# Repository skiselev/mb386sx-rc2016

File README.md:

# Alsea River 386SX Motherboard
An 386SX/486SLC Motherboard based on SARC RC2016 Chipset

## Introduction

The origin of this project is the [M396F motherboard replica by Marco Both](https://github.com/Marco-Both/M396F-Replika). Marco replicated the PCB layout of a certain revision of M396F motherboard. He didn't provide the schematic.

I reverse engineered the schematic based on his PCB layout and made a PCB layout using that schematic similar to the Marco's replica. This was the initial version of this project - [version 1.0](https://github.com/skiselev/mb386sx-rc2016/tree/v1.0).

The subsequent versions contain the following improvements:

* Use Dallas DS12885 RTC/NVRAM (aka CMOS) with a CR2032 battery instead of Motorola MC146818 with a NiCad battery. This reduces the likliehood of motherboard damage due to a leaking battery. A more modern RTC IC also reduces the number of components
* Use SST39SF010A Flash ROM instead of an EPROM or OTP ROM. The Flash ROM is in-circuit programmable, allowing BIOS and BIOS extension upgrades. It has a bigger 128 KiB capacity, all of which is mapped to the CPU memory. The SST39SF010A is a currently manufactured part
* Use PS/2 compatible keyboard controller, VIA VT82C42N or similar. The motherboard implements a dual PS/2 port with both keyboard and mouse signals. A PS/2 keyboard/mouse splitter cable can be used to connect both a keyboard and a mouse.
* Use ATX case compatible mounting holes placement. Implement ATX power supply power on circuit. This allows using the motherboard with more modern ATX cases and power supplies
* Use DIP-8 / half-can crystal oscillators for the CPU and FPU clocks. This removes the need for a difficult to get clock synthesizer IC used in the original motherboard, while still allowing changing the CPU and the FPU clock by switching the oscillators
* Implement headers for the CPU. The CPU can be either installed on a [386SX Universal Socket Adapter](https://github.com/skiselev/i386sx-socket), or soldered down on the motherboard
* On board disagnostic LEDs, Power, and Reset switches

## Status

* Board version 2.3 tested and works properly.
* Board version 2.2 has the fix for the BIOS /OE issue, but it has not been actually built and tested yet.
* Board version 2.1 boots up to BIOS, DOS, and Linux, after performing the fix described in the Known Issues section.
* The following CPUs have been tested with the board version 2.1:
  * Intel 386SX, part name: NG80386SX33. Installed on a 386SX Universal Socket Adapter, configured for 5V. Runs well at 33 MHz.
  * Texas Instruments 486SLCX2-50, part name: TI486SXLC2-G50-WN. Installed on a 386SX Universal Socket Adapter, configured for 3.3V. Runs well at 25 MHz, 33 MHz, and 40 MHz. Unable to enable clock doubling yet.
  * Texas Instruments 486SLCX2-50, part name: TI486SXLC2-G50-PQ. Installed on a 386SX Universal Socket Adapter, configured for 3.3V. Runs well at 25 MHz, 33 MHz, and 40 MHz. Unable to enable clock doubling yet.
  * Texas Instruments 486SLC/E-33. part name: TX486SLC/E-33PAF. Installed on a 386SX Universal Socket Adapter, configured for 5V. Runs well at 33 MHz. Also works at 40 MHz, although gets quite hot. Stability has not been verified yet with 40 MHz.
* PS/2 mouse tested and works properly with both 2 button and 3 button wheeled mouse using [CuteMouse driver](https://cutemouse.sourceforge.net/).
* AMI BIOS 5.10 and [Award BIOS 4.50](https://github.com/skiselev/mb386sx-rc2016/tree/main/BIOS) from other SARC RC2016 based motherboards tested. The latter provides better configurability using MODBIN.

## Hardware Documentation

* [Alsea River 386SX Motherboard - User Guide](User_Guide.md)
* [SARC RC2016 Chipset](SARC_RC2016.md)
* [Cyrix and TI 486SLC/SXLC Processors](Cyrix_and_TI_486.md)

### Schematic and PCB Layout

* [Schematic - Version 2.3](KiCad/AT386SX-Schematic-2.3.pdf)
* [PCB Layout - Version 2.3](KiCad/AT386SX-Board-2.3.pdf)

### Bill of Materials

#### Version 2.3

[Alsea River 386SX Motherboard project on Mouser.com](https://www.mouser.com/Tools/Project/Share?AccessID=6eadf3eb2e) - View and order most components except of the CPU, chipset, keyboard controller, SIMM-30 sockets, and the PCB.

Component type     | Reference | Description                                          | Quantity | Possible sources and notes 
------------------ | --------- | ---------------------------------------------------- | -------- | --------------------------
PCB                |           | Alsea River 386SX PCB - Version 2.1                  | 1        | Order from a PCB manufacturer of your choice using provided Gerber or KiCad files
Integrated Circuit | U1        | 386SX CPU, TI486SXLC, Cx486SLC CPU, 100 pin BQFP     | 1        | eBay
Integrated Circuit | U2        | 387SX FPU or compatible, 68 pin PLCC                 | 1        | eBay. Optional
Integrated Circuit | U3        | SARC RC2016A5, 208 pin PQFP                          | 1        | UTsource
Integrated Circuit | U4        | DS12885 RTC, 24 pin DIP                              | 1        | Mouser [700-DS12885](https://www.mouser.com/ProductDetail/700-DS12885)
Integrated Circuit | U5        | VT82C42N keyboard/mouse controller, 40 pin DIP       | 1        | eBay
Integrated Circuit | U6        | SST39SF010A 128 KiB Flash ROM, 32 pin DIP            | 1        | Mouser [804-39SF010A7CPHE](https://www.mouser.com/ProductDetail/804-39SF010A7CPHE)
Integrated Circuit | U7        | 74HC05 inverters with open drain outputs, 14 pin DIP | 1        | Mouser [595-SN74AHC05N](https://www.mouser.com/ProductDetail/595-SN74AHC05N), [595-SN74HC05N](https://www.mouser.com/ProductDetail/595-SN74HC05N), [595-SN74LS06N](https://www.mouser.com/ProductDetail/595-SN74LS06N)
Integrated Circuit | U8        | 74HCT14 inverters with Schmitt trigger inputs, 14 pin DIP | 1   | Mouser [595-SN74AHCT14N](https://www.mouser.com/ProductDetail/595-SN74AHCT14N), [595-SN74HCT14N](https://www.mouser.com/ProductDetail/595-SN74HCT14N)
Integrated Circuit | U9        | 74HCT74 D-flip flops, 14 pin DIP                     | 1        | Mouser [595-SN74AHCT74N](https://www.mouser.com/ProductDetail/595-SN74AHCT74N), [595-SN74HCT74N](https://www.mouser.com/ProductDetail/595-SN74HCT74N), 
Integrated Circuit | U10       | LM7905 -5V voltage regulator, TO-220-3               | 1        | Mouser [863-MC7905CTG](https://www.mouser.com/ProductDetail/863-MC7905CTG), [926-LM7905CT/NOPB](https://www.mouser.com/ProductDetail/926-LM7905CT-NOPB)
Transistor         | Q1        | 2N3904, NPN transistor, TO-92                        | 1        | Mouser [512-2N3904TA](https://www.mouser.com/ProductDetail/512-2N3904TA)
LED                | D1        | 3 mm LED, blue                                       | 1        | Optional. Mouser [604-WP710A10QBD/D](https://www.mouser.com/ProductDetail/604-WP710A10QBD-D), [696-SSL-LX3054USBD](https://www.mouser.com/ProductDetail/696-SSL-LX3054USBD), [749-3BWD-S](https://www.mouser.com/ProductDetail/749-3BWD-S)
LED                | D2        | 3 mm LED, bi-color red/green                         | 1        | Optional. Mouser [604-WP937EGW](https://www.mouser.com/ProductDetail/604-WP937EGW), [696-SSL-LX3054IGW](https://www.mouser.com/ProductDetail/696-SSL-LX3054IGW), [749-3BC](https://www.mouser.com/ProductDetail/749-3BC)
LED Spacer         | D1, D2    | Spacer for 3 mm LEDs, 3mm height                     | 2        | Optional. Mouser [749-ELM-2-3MM](https://www.mouser.com/ProductDetail/749-ELM-2-3MM)
Crystal Oscillator | X1        | 66 MHz (twice desired CPU frequency), 5V, DIP-8      | 1        | Mouser 50 MHz: [520-TCH5000](https://www.mouser.com/ProductDetail/520-TCH5000), [815-ACH-50-EK](https://www.mouser.com/ProductDetail/815-ACH-50-EK), [774-MXO45HS-3C-50.0](https://www.mouser.com/ProductDetail/774-MXO45HS-3C-50.0); 66.6666MHz: [774-MXO45HS2C66.6666](https://www.mouser.com/ProductDetail/774-MXO45HS2C66.6666), [520-TCH6666-X](https://www.mouser.com/ProductDetail/520-TCH6666-X); 80 MHz: [520-ECS-2200B-800](https://www.mouser.com/ProductDetail/520-ECS-2200B-800), [774-MXO45HS-3C-80.0](https://www.mouser.com/ProductDetail/774-MXO45HS-3C-80.0)
Crystal Oscillator | X2        | 66 MHz (twice desired FPU frequency), 5V, DIP-8      | 1        | Optional. See above.
Crystal Resonator  | Y1        | 14.31818 MHz, parallel, HC-49U                       | 1        | Mouser [815-ABL-14.31818B2](https://www.mouser.com/ProductDetail/815-ABL-14.31818B2), [559-FOXS143-20-LF](https://www.mouser.com/ProductDetail/559-FOXS143-20-LF)
Crystal Resonator Insulator | Y1 | Mylar insulator for HC-49U crystal resonators      | 1        | Optional. Mouser [749-CI-192-028-SR](https://www.mouser.com/ProductDetail/749-CI-192-028-SR)
Crystal Resonator  | Y2        | 32768 Hz, watch crystal, 6 pf, D = 2.1 mm, L = 6.2 mm  | 1      | Mouser [815-AB26T32768KHZ6B](https://www.mouser.com/ProductDetail/815-AB26T32768KHZ6B), [520-ECS327-6-13-X](https://www.mouser.com/ProductDetail/520-ECS327-6-13-X), or [628-VT200F-6PF20PPM](https://www.mouser.com/ProductDetail/628-VT200F-6PF20PPM)
IC Socket          | U2        | 68 pin PLCC, through hole                            | 1        | Mouser [737-PLCC-68-AT](https://www.mouser.com/ProductDetail/737-PLCC-68-AT), [517-8468-11B1-RK-TP](https://www.mouser.com/ProductDetail/517-8468-11B1-RK-TP), [575-682444](https://www.mouser.com/ProductDetail/575-682444)
IC Socket          | U4        | 24 pin DIP                                           | 1        | Mouser [737-ICS-624-T](https://www.mouser.com/ProductDetail/737-ICS-624-T), [517-4824-6000-CP](https://www.mouser.com/ProductDetail/517-4824-6000-CP), [571-1-2199298-8](https://www.mouser.com/ProductDetail/571-1-2199298-8)
IC Socket          | U5        | 40 pin DIP                                           | 1        | Mouser [737-ICS-640-T](https://www.mouser.com/ProductDetail/737-ICS-640-T), [517-4840-6000-CP](https://www.mouser.com/ProductDetail/517-4840-6000-CP), [571-1-2199299-5](https://www.mouser.com/ProductDetail/571-1-2199299-5)
IC Socket          | U6        | 32 pin DIP                                           | 1        | Mouser [737-ICS-632-T](https://www.mouser.com/ProductDetail/737-ICS-632-T), [517-4832-6000-CP](https://www.mouser.com/ProductDetail/517-4832-6000-CP), [571-1-2199300-2](https://www.mouser.com/ProductDetail/571-1-2199300-2)
IC Socket          | U7 - U9   | 14 pin DIP                                           | 3        | Mouser [737-ICS-314-T](https://www.mouser.com/ProductDetail/737-ICS-314-T), [517-4814-3000-CP](https://www.mouser.com/ProductDetail/517-4814-3000-CP), [571-1-2199298-3](https://www.mouser.com/ProductDetail/571-1-2199298-3)
Oscillator Socket  | X1, X2    | 4 pin DIP                                            | 2        | Mouser [535-1108800](https://www.mouser.com/ProductDetail/535-1108800)
Battery            | BT1       | CR2032 battery                                       | 1        | Mouser [81-CR2032](https://www.mouser.com/ProductDetail/81-CR2032), [658-CR2032](https://www.mouser.com/ProductDetail/658-CR2032), [614-CR2032-200](https://www.mouser.com/ProductDetail/614-CR2032-200)
Battery Socket     | BT1       | CR2032 battery socket, through hole                  | 1        | Mouser [122-2420-GR](https://www.mouser.com/ProductDetail/122-2420-GR), [122-2620-GR](https://www.mouser.com/ProductDetail/122-2620-GR)
Connector          | J1 - J4   | SIMM 30 socket, 30 pin                               | 4        | eBay
Connector          | J5 - J10  | ISA card edge connector, 98 pin                      | 6        | Mouser [587-395-098-520-350](https://www.mouser.com/ProductDetail/587-395-098-520-350)
Connector          | J11       | PS/2 Keyboard/Mouse connector, Mini-DIN 6 pin        | 1        | Mouser [806-KMDGX-6S-BS](https://www.mouser.com/ProductDetail/806-KMDGX-6S-BS)
Connector          | J12       | ATX power connector, 20 pin                          | 1        | Mouser [538-46015-2006](https://www.mouser.com/ProductDetail/538-46015-2006)
Connector          | J13       | 2x8 pin header, 2.54 mm (0.1") pitch, through hole   | 1        | Mouser [737-PH2-16-UA](https://www.mouser.com/ProductDetail/737-PH2-16-UA)
Connector          | J14 - J17 | 2x14 pin socket, 2 mm pitch, through hole            | 4        | Optional. Mouser [538-79107-7062](https://www.mouser.com/ProductDetail/538-79107-7062), [200-SQT11301LD](https://www.mouser.com/ProductDetail/200-SQT11301LD), [200-SQT11301FD](https://www.mouser.com/ProductDetail/200-SQT11301FD)
Connector          | JP1 - JP3 | 2 pin header, 2.54 mm (0.1") pitch, through hole     | 3        | Mouser [737-PH1-02-UA](https://www.mouser.com/ProductDetail/737-PH1-02-UA)
Connector          | JP4 - JP6 | 3 pin header, 2.54 mm (0.1") pitch, through hole     | 3        | Mouser [737-PH1-03-UA](https://www.mouser.com/ProductDetail/737-PH1-03-UA). Some headers are optional, and can be hardwired for the soldered CPU.
Connector          | JP1 - JP6 | Shunt, 2 pin, 2.54 mm (0.1") pitch                   | 4        | Mouser [737-MSA-G](https://www.mouser.com/ProductDetail/737-MSA-G), [806-SX1100-B](https://www.mouser.com/ProductDetail/806-SX1100-B)
Switch             | SW1, SW2  | 6 mm tactile switch, vertical, through hole          | 2        | Optional. Mouser [653-B3F-1000](https://www.mouser.com/ProductDetail/653-B3F-1000)
Capacitor          | C1 - C3   | 30 pF, 50V MLCC, 5.08 mm (0.2") pitch                | 3        | Mouser [594-K300J10C0GF5UH5](https://www.mouser.com/ProductDetail/594-K300J10C0GF5UH5)
Capacitor          | C4 - C7   | 47 pF, 50V MLCC, 5.08 mm (0.2") pitch                | 4        | Mouser [810-FG28C0G1H470JNT6](https://www.mouser.com/ProductDetail/810-FG28C0G1H470JNT6)
Capacitor          | C8        | 100 pF, 50V MLCC, 5.08 mm (0.2") pitch               | 1        | Mouser [810-FG28C0G1H101JNT6](https://www.mouser.com/ProductDetail/810-FG28C0G1H101JNT6)
Capacitor          | C9        | 220 pF, 50V MLCC, 5.08 mm (0.2") pitch               | 1        | Mouser [810-FG28C0G1H221JNT6](https://www.mouser.com/ProductDetail/810-FG28C0G1H221JNT6)
Capacitor          | C10 - C21 | 100 nF, 25V MLCC, 5.08 mm (0.2") pitch               | 12       | Mouser [594-K104K15X7RF53H5](https://www.mouser.com/ProductDetail/594-K104K15X7RF53H5), [810-FG28X7R1H104KNT6](https://www.mouser.com/ProductDetail/810-FG28X7R1H104KNT6)
Capacitor          | C22, C23  | 1 uF, 10V MLCC, 5.08 mm (0.2") pitch                 | 2        | Mouser [810-FG28X5R1H105KRT6](https://www.mouser.com/ProductDetail/810-FG28X5R1H105KRT6)
Capacitor          | C24 - C48 | 10 uF, 25V electrolytic, 5 mm diameter, 2.5 mm pitch | 25       | Mouser [667-EEU-FR1H100](https://www.mouser.com/ProductDetail/667-EEU-FR1H100)
Polyfuse           | F1        | 1.1A, 5.08 mm (0.2") pitch                           | 1        | Mouser [650-RUSBF110-2](https://www.mouser.com/ProductDetail/650-RUSBF110-2)
Ferrite Choke      | L1 - L4   | axial                                                | 4        | Mouser [623-2743001112LF](https://www.mouser.com/ProductDetail/623-2743001112LF)
Resistor           | R1 - R12  | 10 ohm, 0.25 W, axial                                | 12       | Mouser [708-CF14JT10R0](https://www.mouser.com/ProductDetail/708-CF14JT10R0), [603-MFR-25FBF52-10R](https://www.mouser.com/ProductDetail/603-MFR-25FBF52-10R)
Resistor           | R13 - R15 | 22 ohm, 0.25 W, axial                                | 3        | Mouser [708-CF14JT22R0](https://www.mouser.com/ProductDetail/708-CF14JT22R0), [603-MFR-25FBF52-22R](https://www.mouser.com/ProductDetail/603-MFR-25FBF52-22R)
Resistor           | R16, R17  | 56 ohm, 0.25 W, axial                                | 2        | Mouser [708-CF14JT56R0](https://www.mouser.com/ProductDetail/708-CF14JT56R0), [603-MFR-25FBF52-56R](https://www.mouser.com/ProductDetail/603-MFR-25FBF52-56R)
Resistor           | R18 - R21 | 100 ohm, 0.25 W, axial                               | 4        | Mouser [708-CF14JT100R](https://www.mouser.com/ProductDetail/708-CF14JT100R), [603-MFR-25FBF52-100R](https://www.mouser.com/ProductDetail/603-MFR-25FBF52-100R)
Resistor           | R22       | 330 ohm, 0.25 W, axial                               | 1        | Mouser [708-CF14JT330R](https://www.mouser.com/ProductDetail/708-CF14JT330R), [603-MFR-25FBF52-330R](https://www.mouser.com/ProductDetail/603-MFR-25FBF52-330R)
Resistor           | R23 - R29 | 470 ohm, 0.25 W, axial                               | 7        | Mouser [708-CF14JT470R](https://www.mouser.com/ProductDetail/708-CF14JT470R), [603-MFR-25FBF52-470R](https://www.mouser.com/ProductDetail/603-MFR-25FBF52-470R)
Resistor           | R30, R31  | 1 kohm, 0.25 W, axial                                | 2        | Mouser [708-CF14JT1K00](https://www.mouser.com/ProductDetail/708-CF14JT1K00), [603-MFR-25FBF52-1K](https://www.mouser.com/ProductDetail/603-MFR-25FBF52-1K)
Resistor           | R32       | 4.7 kohm, 0.25 W, axial                              | 1        | Mouser [708-CF14JT4K70](https://www.mouser.com/ProductDetail/708-CF14JT4K70), [603-MFR-25FBF52-4K7](https://www.mouser.com/ProductDetail/603-MFR-25FBF52-4K7)
Resistor           | R33 - R38 | 10 kohm, 0.25 W, axial                               | 6        | Mouser [708-CF14JT10K0](https://www.mouser.com/ProductDetail/708-CF14JT10K0), [603-MFR-25FBF52-10K](https://www.mouser.com/ProductDetail/603-MFR-25FBF52-10K)
Resistor           | R39       | 22 kohm, 0.25 W, axial                               | 1        | Mouser [708-CF14JT22K0](https://www.mouser.com/ProductDetail/708-CF14JT22K0), [603-MFR-25FBF52-22K](https://www.mouser.com/ProductDetail/603-MFR-25FBF52-22K)
Resistor           | R40       | 1 Mohm, 0.25 W, axial                                | 1        | Mouser [708-CF14JT1M00](https://www.mouser.com/ProductDetail/708-CF14JT1M00), [603-MFR-25FBF52-1M](https://www.mouser.com/ProductDetail/603-MFR-25FBF52-1M)
Resistor Array     | RN1       | 330 ohm, 8 resistors, bussed, 9 pin SIL              | 1        | Mouser [652-4609X-1LF-330](https://www.mouser.com/ProductDetail/652-4609X-1LF-330), [652-4609X-AP1-331LF](https://www.mouser.com/ProductDetail/652-4609X-AP1-331LF)
Resistor Array     | RN2, RN3  | 4.7 kohm, 5 resistors, bussed, 6 pin SIL             | 2        | Mouser [652-4606X-1LF-4.7K](https://www.mouser.com/ProductDetail/652-4606X-1LF-4.7K), [652-4606X-AP1-472LF](https://www.mouser.com/ProductDetail/652-4606X-AP1-472LF)
Resistor Array     | RN4       | 4.7 kohm, 8 resistors, bussed, 9 pin SIL             | 1        | Mouser [652-4609X-1LF-4.7K](https://www.mouser.com/ProductDetail/652-4609X-1LF-4.7K), [652-4609X-AP1-472LF](https://www.mouser.com/ProductDetail/652-4609X-AP1-472LF)
Resistor Array     | RN5       | 10 kohm, 4 resistors, bussed, 5 pin SIL              | 1        | Mouser [652-4605X-1LF-10K](https://www.mouser.com/ProductDetail/652-4605X-1LF-10K), [652-4605X-AP1-103LF](https://www.mouser.com/ProductDetail/652-4605X-AP1-103LF)

## Software

### BIOS

For the testing purposes I am using BIOSes from other commerical motherboards based on the same SARC RC2016 chipset. [The Retro Web](https://theretroweb.com/bios?itemsPerPage=24&chipsetIds[]=648) has a collection of the BIOSes for this chipset.

#### BIOS Progamming and ROM ICs support.

The is designed for the 128 KiB SST SST39SF010A Flash ROM. This ROM is mapped to the 0xE0000-0xFFFFF (or, with 8086 segments, E000:0000 to F000:FFFF). The upper 64 KiB - 0xF0000-0xFFFFF (F000:0000-F000:FFFF) are typically used for the BIOS ROM. The lower 64 KiB - 0xE0000-0xEFFFF can be used for BIOS extensions. Please take that into the consideration when programming the Flash ROM. Make sure to load the BIOS image to the top 64 KiB of the Flash ROM, starting at the address 0x10000. Other pin compatible 128 KiB Flash ROMs, such as AMD AM29F010A, SST SST29EE010, Atmel AT29C010A can be also used without any changes.

It is also possible to use 256 KiB and 512 KiB Flash ROMs, for example SST39SF020 and SST39SF040. Note that the A17 address line is connected to VCC (logic high/"1") and the address line A18 is connected to the ground (logic low/"0"). Therefore when using these flash ROMs, please program the 64 KiB BIOS image starting at the addres 0x30000 of the Flash ROM.

Finally, the board also should work with 64 KiB EPROMs and OTP ROMs, e.g., 27C512. In this case, install the EPROM to the right side of the socket, that is pin 1 of the EPROM should go to the pin 3 of the socket.

## Changes

* Version 2.3
  * Use non-plated through holes for the plastic posts of SIMM30 sockets
  * Ground the shield of the PS/2 connector
  * Update silkscreen: Add acknowledgements, move references and values of DRAM resistors to make them more visible
  * Update schematic: Update a few pins on the RC2016A symbol

* Version 2.2
  * Fix the Flash ROM /OE issue: Connect Flash ROM /OE to ISA /MEMR
  * Renumber DRAM banks - swap Bank 0 and Bank 1. Rename DRAM signals accordingly
  * Add CPU pin 1 marking on the silkscreen
  * Renumber SIMM and ISA slots, so that the reference numbers increase from the top of the PCB to the bottom
  * Renumber electrolytic capacitors, so that the reference numbers increase from the top of the PCB to the bottom
  * Use 22 kohm resistor for R39
  * Remove load capacitors on the ISA bus signals, that are not populated anyway
  * Add a polyfuse for the PS/2 port

* Version 2.1
  * Renumber the component references according to the values and locations on the PCB
  * Update silkscreen
  * Add signal names on the back silkscreen

* Version 2.0
  * Use ATX power supply connector
  * Add ATX power-on circuit

* Version 1.9
  * Add pin headers for the CPU

* Version 1.8
  * Connect /OE and /WE of the BIOS ROM to allow Flash ROM in-system programming
  * Rotate the PCB into portrait orientation

* Version 1.7
  * Use single front panel connector

* Version 1.6
  * Use a low profile 14.31818 MHz crystal (or an SMD part)
  * Add support for the separate FPU clock
  * Use half can oscillators for the CPU and the FPU clocks
  * Use discrete resistors for DRAM interface
  * Use resistors with 300 mil (7.62 mm) lead spacing
  * Move R23 down closer to JP8

* Version 1.5
  * Add more 10 uF filtering capacitors to the power rails
  * Remove extra capacitors for /IOW and RESET signals (use capacitors between two leftmost ISA slots
  * Use resistor arrays for SA17-SA19 pull-ups

* Version 1.4
  * Increase board depth by 0.1". Move mount holes to ATX compatible locations

* Version 1.3
  * Wire keyboard controller in PS/2 mode. Use PS/2 Mini-Din connector in a PS/2 dualport configuration

* Version 1.2
  * Add support for 128 KiB Flash ROM ICs for BIOS. SST39SF010A or similar.
 
* Version 1.1
  * Use DS12885 RTC with CR2032 coin cell battery

* Version 1.0
  * Reverse engineered schematic of M396F motherboard
  * PCB layout closely based on the original M396F layout with a few minor changes

## Known Issues

* Versions 1.8 - 2.1
  * The board will not boot into the BIOS.
    * Workaround: Cut the trace going to the Flash ROM pin 24. Solder a wire to connect the flash ROM /OE signal, pin 24 to the ISA /MEMR signal, ISA bus pin 89.
    * The issue happens because following the reset, 386SX fetches instructions starting from address 0xFFFFF0 - the last 16 bytes of its 16 MiB address space. But the board uses /SMEMR signal for the Flash ROM /OE, and that signal is only generated when reading the first megabyte of memory. So the BIOS ROM does not get the /OE signal.

* Versions 1.0 - 2.1
  * DRAM bank 0 and bank 1 swapped around. Bank 0 is the one closer to the edge of the board.

## Wishlist

* On-board speaker
* Try using more common values for C1 - C2: 27 pF or 33 pF are more commonly available than 30 pF
* 3.3V CPU support
  * The current plan is to test this using the [386SX Universal Socket Adapter](https://github.com/skiselev/i386sx-socket)
  * Separate VCC plane for the CPU
  * Linear voltage regulator
  * Solder jumpers to bypass the voltage regulator and connect the CPU to 5V
* 4 layer PCB
  * VCC and ground planes
* Consider using SMD components

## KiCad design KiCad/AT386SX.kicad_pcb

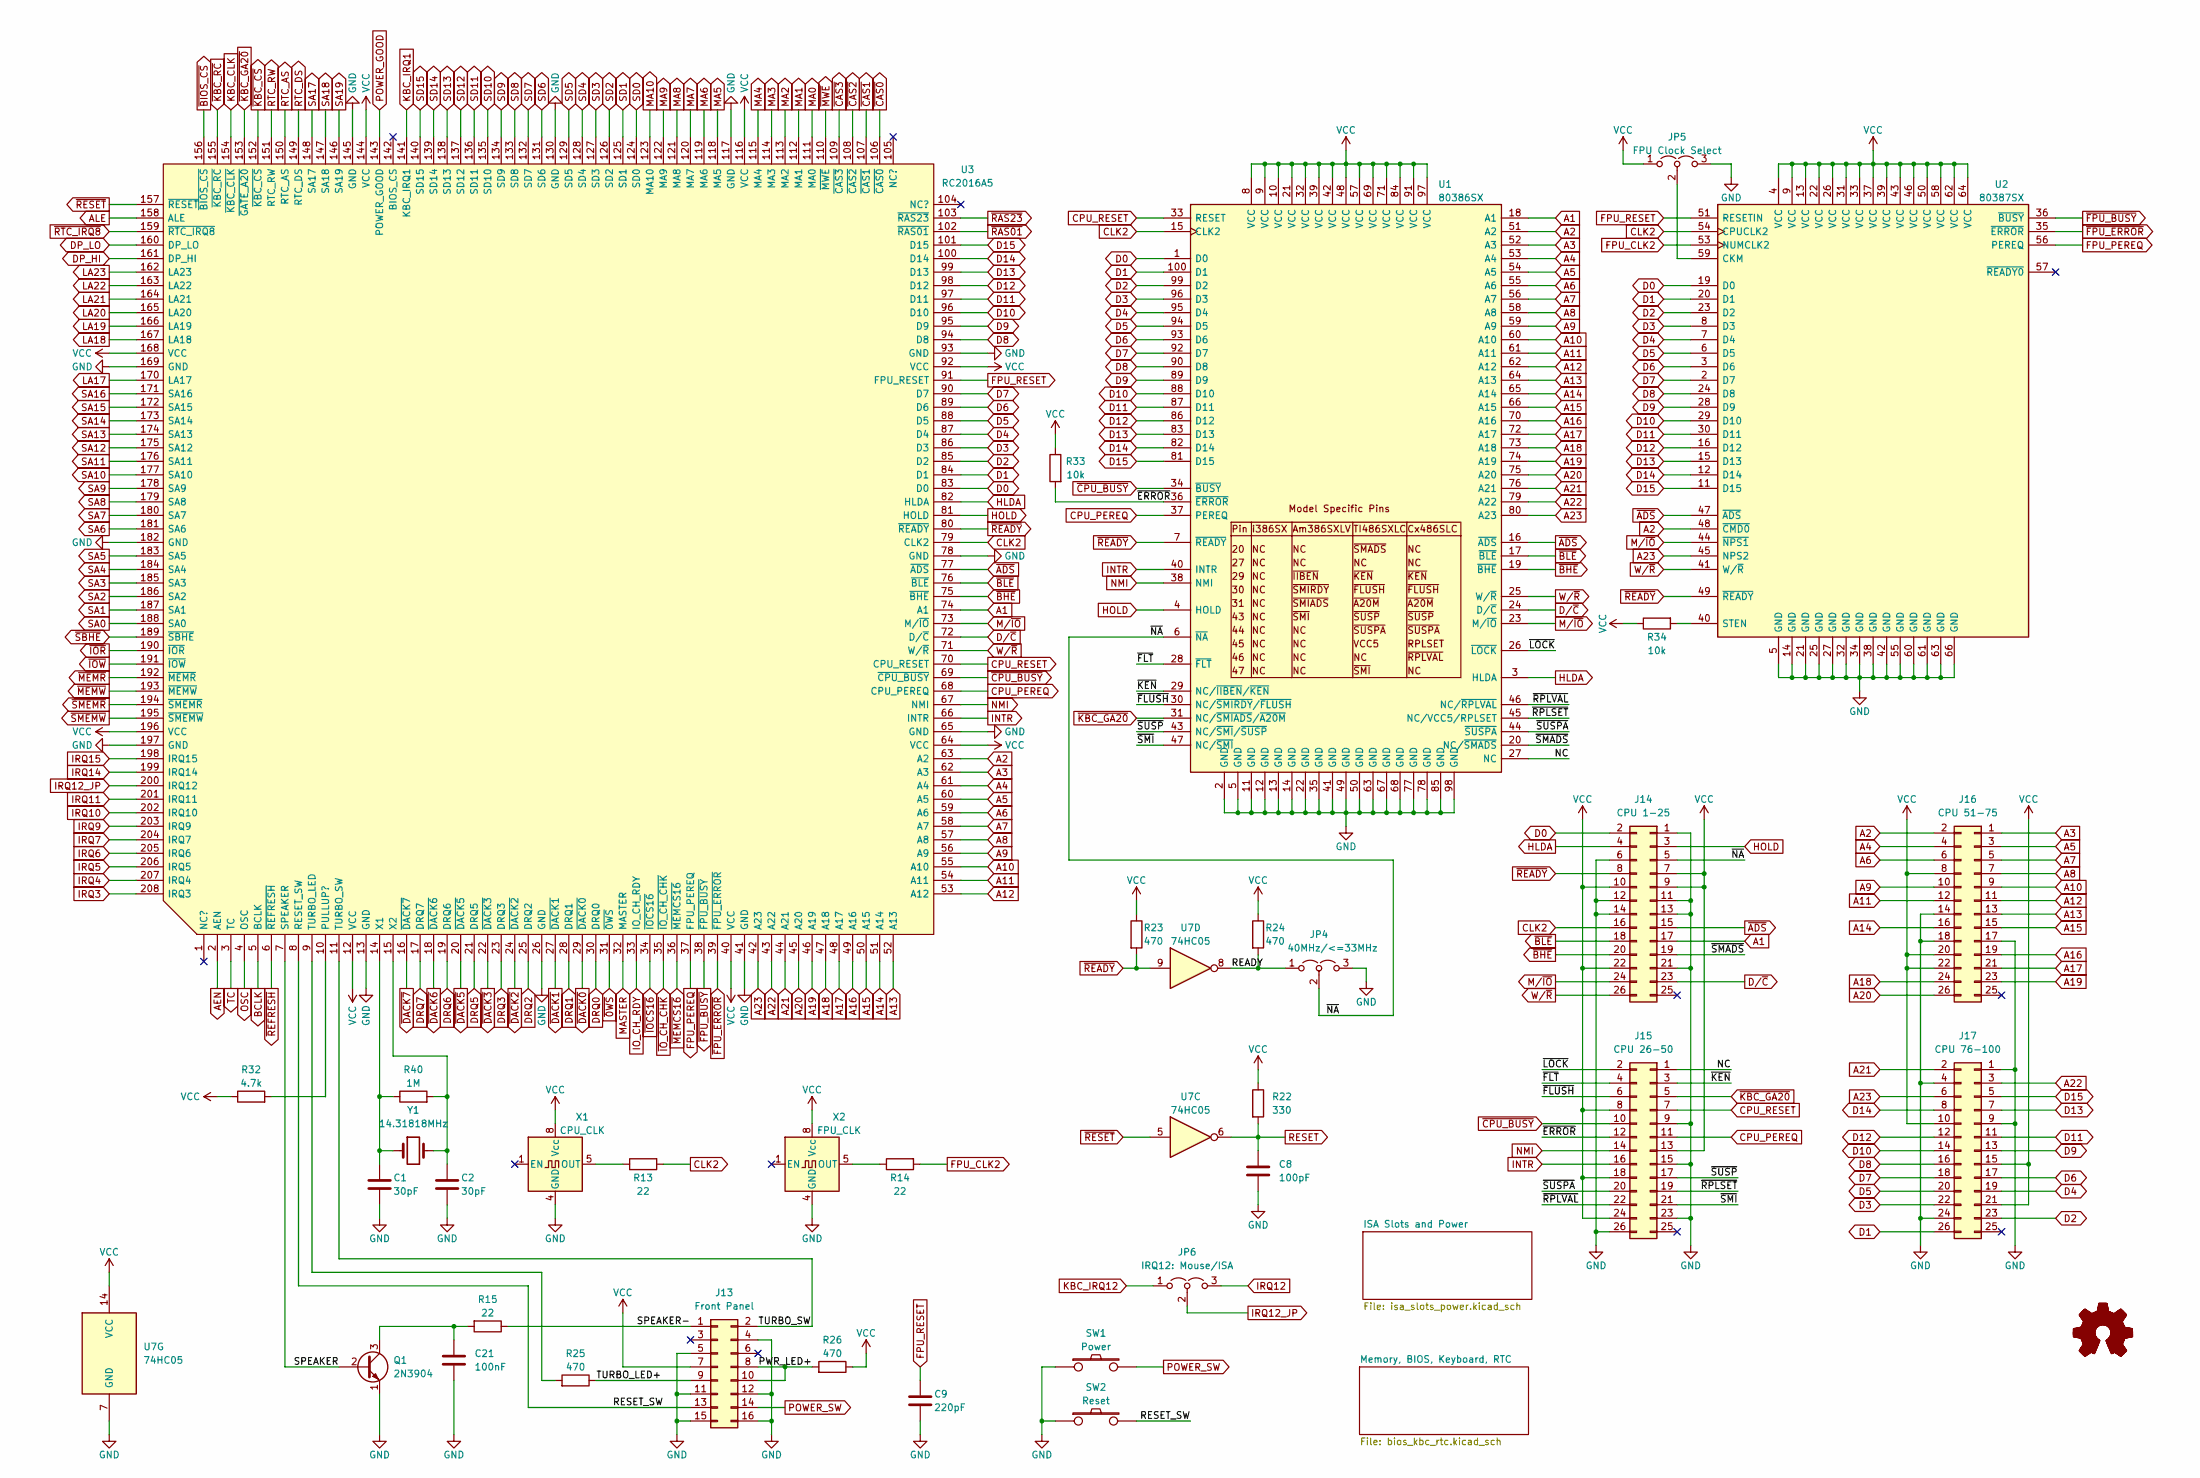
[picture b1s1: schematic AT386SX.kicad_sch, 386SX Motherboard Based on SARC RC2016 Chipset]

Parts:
C1, C2: 30pF; Cap_Cer_508
C8: 100pF; Cap_Cer_508
C9: 220pF; Cap_Cer_508
C21: 100nF; Cap_Cer_508
J13: Front Panel; Conn_Pin_Header_8x2_2.54mm
J14: CPU 1-25; PinHeader_2x13_P2.00mm_Vertical
J15: CPU 26-50; PinHeader_2x13_P2.00mm_Vertical
J16: CPU 51-75; PinHeader_2x13_P2.00mm_Vertical
J17: CPU 76-100; PinHeader_2x13_P2.00mm_Vertical
JP4: 40MHz/<=33MHz; Conn_Pin_Header_3x1_2.54mm
JP5: FPU Clock Select; Conn_Pin_Header_3x1_2.54mm
JP6: IRQ12: Mouse/ISA; Conn_Pin_Header_3x1_2.54mm
LOGO1: Logo_Open_Hardware_Small; OSHW-Logo2_7.3x6mm_SilkScreen
LOGO2: Logo_Open_Hardware_Small; KiCad-Logo2_5mm_SilkScreen
Q1: 2N3904; Transistor_TO92_EBC_254
R13, R14, R15: 22; Res_762
R22: 330; Res_762
R23, R24, R25, R26: 470; Res_762
R32: 4.7k; Res_762
R33, R34: 10k; Res_762
R40: 1M; Res_762
SW1: Power; Switch_Tactile_6mm
SW2: Reset; Switch_Tactile_6mm
U1: 80386SX; PQFP-100_19x19mm_P0.635mm_i386sx
U2: 80387SX; IC_PLCC68_INTEL_TH
U3: RC2016A5; PQFP-208_28x28mm_P0.5mm
U7: 74HC05; IC_DIP14_300
X1: CPU_CLK; OSC_Half_Can_DIP8
X2: FPU_CLK; OSC_Half_Can_DIP8
Y1: 14.31818MHz; Crystal_HC-49U_Vert

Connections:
/NC: J15.1, U1.27 (NC)
/PWR_LED+: J13.8, J13.10, R26.2
/READY: JP4.1 (A), R24.2, U7.8
/RESET_SW: J13.13, SW2.2, U3.8 (RESET_SW)
/SPEAKER: Q1.2 (B), U3.7 (SPEAKER)
/SPEAKER-: J13.1, R15.1
/TURBO_LED+: J13.9, R25.1
/TURBO_SW: J13.2, U3.11 (TURBO_SW)
/~ERROR: J15.12, R33.2, U1.36 (~ERROR)
/~FLT: J15.4, U1.28 (~FLT)
/~FLUSH: J15.6, U1.30 (NC/~SMIRDY/~FLUSH)
/~KEN: J15.3, U1.29 (NC/~IIBEN/~KEN)
/~LOCK: J15.2, U1.26 (~LOCK)
/~NA: J14.5, JP4.2 (C), U1.6 (~NA)
/~RPLSET: J15.19, U1.45 (NC/VCC5/RPLSET)
/~RPLVAL: J15.22, U1.46 (NC/~RPLVAL)
/~SMADS: J14.19, U1.20 (NC/~SMADS)
/~SMI: J15.21, U1.47 (NC/~SMI)
/~SUSPA: J15.20, U1.44 (~SUSPA)
/~SUSP: J15.17, U1.43 (NC/~SMI/~SUSP)
A1: J14.17, U1.18 (A1), U3.74 (A1)
A2: J16.2, U1.51 (A2), U2.48 (~CMD0), U3.63 (A2)
A3: J16.1, U1.52 (A3), U3.62 (A3)
A4: J16.4, U1.53 (A4), U3.61 (A4)
A5: J16.3, U1.54 (A5), U3.60 (A5)
A6: J16.6, U1.55 (A6), U3.59 (A6)
A7: J16.5, U1.56 (A7), U3.58 (A7)
A8: J16.7, U1.58 (A8), U3.57 (A8)
A9: J16.10, U1.59 (A9), U3.56 (A9)
A10: J16.9, U1.60 (A10), U3.55 (A10)
A11: J16.12, U1.61 (A11), U3.54 (A11)
A12: J16.11, U1.62 (A12), U3.53 (A12)
A13: J16.13, U1.64 (A13), U3.52 (A13)
A14: J16.16, U1.65 (A14), U3.51 (A14)
A15: J16.15, U1.66 (A15), U3.50 (A15)
A16: J16.19, U1.70 (A16), U3.49 (A16)
A17: J16.21, U1.72 (A17), U3.48 (A17)
A18: J16.24, U1.73 (A18), U3.47 (A18)
A19: J16.23, U1.74 (A19), U3.46 (A19)
A20: J16.26, U1.75 (A20), U3.45 (A20)
A21: J17.2, U1.76 (A21), U3.44 (A21)
A22: J17.3, U1.79 (A22), U3.43 (A22)
A23: J17.6, U1.80 (A23), U2.45 (NPS2), U3.42 (A23)
AEN: U3.2 (AEN); also elsewhere on the board
ALE: U3.158 (ALE); also elsewhere on the board
BCLK: U3.5 (BCLK); also elsewhere on the board
CLK2: J14.16, R13.2, U1.15 (CLK2), U2.54 (CPUCLK2), U3.79 (CLK2)
CPU_PEREQ: J15.11, U1.37 (PEREQ), U3.68 (CPU_PEREQ)
CPU_RESET: J15.7, U1.33 (RESET), U3.70 (CPU_RESET)
D0: J14.2, U1.1 (D0), U2.19 (D0), U3.83 (D0); also elsewhere on the board
D1: J17.26, U1.100 (D1), U2.20 (D1), U3.84 (D1); also elsewhere on the board
D2: J17.23, U1.99 (D2), U2.23 (D2), U3.85 (D2); also elsewhere on the board
D3: J17.22, U1.96 (D3), U2.8 (D3), U3.86 (D3); also elsewhere on the board
D4: J17.19, U1.95 (D4), U2.7 (D4), U3.87 (D4); also elsewhere on the board
D5: J17.20, U1.94 (D5), U2.6 (D5), U3.88 (D5); also elsewhere on the board
D6: J17.17, U1.93 (D6), U2.3 (D6), U3.89 (D6); also elsewhere on the board
D7: J17.18, U1.92 (D7), U2.2 (D7), U3.90 (D7); also elsewhere on the board
D8: J17.16, U1.90 (D8), U2.24 (D8), U3.94 (D8); also elsewhere on the board
D9: J17.13, U1.89 (D9), U2.28 (D9), U3.95 (D9); also elsewhere on the board
D10: J17.14, U1.88 (D10), U2.29 (D10), U3.96 (D10); also elsewhere on the board
D11: J17.11, U1.87 (D11), U2.30 (D11), U3.97 (D11); also elsewhere on the board
D12: J17.12, U1.86 (D12), U2.16 (D12), U3.98 (D12); also elsewhere on the board
D13: J17.7, U1.83 (D13), U2.15 (D13), U3.99 (D13); also elsewhere on the board
D14: J17.8, U1.82 (D14), U2.12 (D14), U3.100 (D14); also elsewhere on the board
D15: J17.5, U1.81 (D15), U2.11 (D15), U3.101 (D15); also elsewhere on the board
DP_HI: U3.161 (DP_HI); also elsewhere on the board
DP_LO: U3.160 (DP_LO); also elsewhere on the board
DRQ0: U3.30 (DRQ0); also elsewhere on the board
DRQ1: U3.28 (DRQ1); also elsewhere on the board
DRQ2: U3.25 (DRQ2); also elsewhere on the board
DRQ3: U3.23 (DRQ3); also elsewhere on the board
DRQ5: U3.21 (DRQ5); also elsewhere on the board
DRQ6: U3.19 (DRQ6); also elsewhere on the board
DRQ7: U3.17 (DRQ7); also elsewhere on the board
D/~C: J14.23, U1.24 (D/~C), U3.72 (D/~C)
FPU_CLK2: R14.2, U2.53 (NUMCLK2)
FPU_PEREQ: U2.56 (PEREQ), U3.37 (FPU_PEREQ)
FPU_RESET: C9.1, U2.51 (RESETIN), U3.91 (FPU_RESET)
GND: C1.2, C2.2, C8.2, C9.2, C21.2, J13.4, J13.5, J13.11, J13.12, J13.15, J13.16, J14.1, J14.6, J14.11, J14.12, J14.13, J14.14, J14.21, J15.9, J15.15, J15.23, J15.26, J16.14, J16.17, J16.18, J17.1, J17.4, J17.9, J17.24, JP4.3 (B), JP5.3 (B), Q1.1 (E), SW1.1, SW2.1, U1.2 (GND), U1.5 (GND), U1.11 (GND), U1.12 (GND), U1.13 (GND), U1.14 (GND), U1.22 (GND), U1.35 (GND), U1.41 (GND), U1.49 (GND), U1.50 (GND), U1.63 (GND), U1.67 (GND), U1.68 (GND), U1.77 (GND), U1.78 (GND), U1.85 (GND), U1.98 (GND), U2.5 (GND), U2.14 (GND), U2.21 (GND), U2.25 (GND), U2.27 (GND), U2.32 (GND), U2.34 (GND), U2.38 (GND), U2.42 (GND), U2.55 (GND), U2.60 (GND), U2.61 (GND), U2.63 (GND), U2.66 (GND), U3.13 (GND), U3.26 (GND), U3.41 (GND), U3.65 (GND), U3.78 (GND), U3.93 (GND), U3.117 (GND), U3.130 (GND), U3.145 (GND), U3.169 (GND), U3.182 (GND), U3.197 (GND), U7.7 (GND), X1.4 (GND), X2.4 (GND); also elsewhere on the board
HLDA: J14.4, U1.3 (HLDA), U3.82 (HLDA)
HOLD: J14.3, U1.4 (HOLD), U3.81 (HOLD)
INTR: J15.16, U1.40 (INTR), U3.66 (INTR)
IO_CH_RDY: U3.33 (IO_CH_RDY); also elsewhere on the board
IRQ3: U3.208 (IRQ3); also elsewhere on the board
IRQ4: U3.207 (IRQ4); also elsewhere on the board
IRQ5: U3.206 (IRQ5); also elsewhere on the board
IRQ6: U3.205 (IRQ6); also elsewhere on the board
IRQ7: U3.204 (IRQ7); also elsewhere on the board
IRQ9: U3.203 (IRQ9); also elsewhere on the board
IRQ10: U3.202 (IRQ10); also elsewhere on the board
IRQ11: U3.201 (IRQ11); also elsewhere on the board
IRQ12: JP6.3 (B); also elsewhere on the board
IRQ12_JP: JP6.2 (C), U3.200 (IRQ12)
IRQ14: U3.199 (IRQ14); also elsewhere on the board
IRQ15: U3.198 (IRQ15); also elsewhere on the board
KBC_CLK: U3.154 (~KBC_CLK); also elsewhere on the board
KBC_IRQ1: U3.141 (KBC_IRQ1); also elsewhere on the board
KBC_IRQ12: JP6.1 (A); also elsewhere on the board
LA17: U3.170 (LA17); also elsewhere on the board
LA18: U3.167 (LA18); also elsewhere on the board
LA19: U3.166 (LA19); also elsewhere on the board
LA20: U3.165 (LA20); also elsewhere on the board
LA21: U3.164 (LA21); also elsewhere on the board
LA22: U3.163 (LA22); also elsewhere on the board
LA23: U3.162 (LA23); also elsewhere on the board
MA0: U3.111 (MA0); also elsewhere on the board
MA1: U3.112 (MA1); also elsewhere on the board
MA2: U3.113 (MA2); also elsewhere on the board
MA3: U3.114 (MA3); also elsewhere on the board
MA4: U3.115 (MA4); also elsewhere on the board
MA5: U3.118 (MA5); also elsewhere on the board
MA6: U3.119 (MA6); also elsewhere on the board
MA7: U3.120 (MA7); also elsewhere on the board
MA8: U3.121 (MA8); also elsewhere on the board
MA9: U3.122 (MA9); also elsewhere on the board
MA10: U3.123 (MA10); also elsewhere on the board
MASTER: U3.32 (MASTER); also elsewhere on the board
M/~IO: J14.24, U1.23 (M/~IO), U2.44 (~NPS1), U3.73 (M/~IO)
NMI: J15.14, U1.38 (NMI), U3.67 (NMI)
unnamed: C1.1, R40.1, U3.14 (X1), Y1.1
unnamed: C2.1, R40.2, U3.15 (X2), Y1.2
unnamed: C21.1, Q1.3 (C), R15.2
unnamed: JP5.2 (C), U2.59 (CKM)
unnamed: R13.1, X1.5 (OUT)
unnamed: R14.1, X2.5 (OUT)
unnamed: R25.2, U3.9 (TURBO_LED)
unnamed: R32.2, U3.10 (PULLUP?)
unnamed: R34.2, U2.40 (STEN)
OSC: U3.4 (OSC); also elsewhere on the board
POWER_GOOD: U3.143 (POWER_GOOD); also elsewhere on the board
POWER_SW: J13.14, SW1.2; also elsewhere on the board
RESET: C8.1, R22.2, U7.6; also elsewhere on the board
RTC_AS: U3.150 (RTC_AS); also elsewhere on the board
RTC_DS: U3.149 (RTC_DS); also elsewhere on the board
RTC_RW: U3.151 (RTC_RW); also elsewhere on the board
SA0: U3.188 (SA0); also elsewhere on the board
SA1: U3.187 (SA1); also elsewhere on the board
SA2: U3.186 (SA2); also elsewhere on the board
SA3: U3.185 (SA3); also elsewhere on the board
SA4: U3.184 (SA4); also elsewhere on the board
SA5: U3.183 (SA5); also elsewhere on the board
SA6: U3.181 (SA6); also elsewhere on the board
SA7: U3.180 (SA7); also elsewhere on the board
SA8: U3.179 (SA8); also elsewhere on the board
SA9: U3.178 (SA9); also elsewhere on the board
SA10: U3.177 (SA10); also elsewhere on the board
SA11: U3.176 (SA11); also elsewhere on the board
SA12: U3.175 (SA12); also elsewhere on the board
SA13: U3.174 (SA13); also elsewhere on the board
SA14: U3.173 (SA14); also elsewhere on the board
SA15: U3.172 (SA15); also elsewhere on the board
SA16: U3.171 (SA16); also elsewhere on the board
SA17: U3.148 (SA17); also elsewhere on the board
SA18: U3.147 (SA18); also elsewhere on the board
SA19: U3.146 (SA19); also elsewhere on the board
SD0: U3.124 (SD0); also elsewhere on the board
SD1: U3.125 (SD1); also elsewhere on the board
SD2: U3.126 (SD2); also elsewhere on the board
SD3: U3.127 (SD3); also elsewhere on the board
SD4: U3.128 (SD4); also elsewhere on the board
SD5: U3.129 (SD5); also elsewhere on the board
SD6: U3.131 (SD6); also elsewhere on the board
SD7: U3.132 (SD7); also elsewhere on the board
SD8: U3.133 (SD8); also elsewhere on the board
SD9: U3.134 (SD9); also elsewhere on the board
SD10: U3.135 (SD10); also elsewhere on the board
SD11: U3.136 (SD11); also elsewhere on the board
SD12: U3.137 (SD12); also elsewhere on the board
SD13: U3.138 (SD13); also elsewhere on the board
SD14: U3.139 (SD14); also elsewhere on the board
SD15: U3.140 (SD15); also elsewhere on the board
TC: U3.3 (TC); also elsewhere on the board
VCC: J13.7, J14.7, J14.9, J14.10, J14.22, J15.8, J15.13, J15.18, J15.24, J16.8, J16.20, J16.22, J17.10, J17.15, J17.21, JP5.1 (A), R22.1, R23.1, R24.1, R26.1, R32.1, R33.1, R34.1, U1.8 (VCC), U1.9 (VCC), U1.10 (VCC), U1.21 (VCC), U1.32 (VCC), U1.39 (VCC), U1.42 (VCC), U1.48 (VCC), U1.57 (VCC), U1.69 (VCC), U1.71 (VCC), U1.84 (VCC), U1.91 (VCC), U1.97 (VCC), U2.4 (VCC), U2.9 (VCC), U2.13 (VCC), U2.22 (VCC), U2.26 (VCC), U2.31 (VCC), U2.33 (VCC), U2.37 (VCC), U2.39 (VCC), U2.43 (VCC), U2.46 (VCC), U2.50 (VCC), U2.58 (VCC), U2.62 (VCC), U2.64 (VCC), U3.12 (VCC), U3.40 (VCC), U3.64 (VCC), U3.92 (VCC), U3.116 (VCC), U3.144 (VCC), U3.168 (VCC), U3.196 (VCC), U7.14 (VCC), X1.8 (Vcc), X2.8 (Vcc); also elsewhere on the board
W/~R: J14.26, U1.25 (W/~R), U2.41 (W/~R), U3.71 (W/~R)
~0WS: U3.31 (~0WS); also elsewhere on the board
~ADS: J14.15, U1.16 (~ADS), U2.47 (~ADS), U3.77 (~ADS)
~BHE: J14.20, U1.19 (~BHE), U3.75 (~BHE)
~BIOS_CS: U3.156 (~BIOS_CS); also elsewhere on the board
~BLE: J14.18, U1.17 (~BLE), U3.76 (~BLE)
~CAS0: U3.106 (~CAS0); also elsewhere on the board
~CAS1: U3.107 (~CAS1); also elsewhere on the board
~CAS2: U3.108 (~CAS2); also elsewhere on the board
~CAS3: U3.109 (~CAS3); also elsewhere on the board
~CPU_BUSY: J15.10, U1.34 (~BUSY), U3.69 (~CPU_BUSY)
~DACK0: U3.29 (~DACK0); also elsewhere on the board
~DACK1: U3.27 (~DACK1); also elsewhere on the board
~DACK2: U3.24 (~DACK2); also elsewhere on the board
~DACK3: U3.22 (~DACK3); also elsewhere on the board
~DACK5: U3.20 (~DACK5); also elsewhere on the board
~DACK6: U3.18 (~DACK6); also elsewhere on the board
~DACK7: U3.16 (~DACK7); also elsewhere on the board
~FPU_BUSY: U2.36 (~BUSY), U3.38 (~FPU_BUSY)
~FPU_ERROR: U2.35 (~ERROR), U3.39 (~FPU_ERROR)
~IOCS16: U3.34 (~IOCS16); also elsewhere on the board
~IOR: U3.190 (~IOR); also elsewhere on the board
~IOW: U3.191 (~IOW); also elsewhere on the board
~IO_CH_CHK: U3.35 (~IO_CH_CHK); also elsewhere on the board
~KBC_CS: U3.152 (~KBC_CS); also elsewhere on the board
~KBC_GA20: J15.5, U1.31 (NC/~SMIADS/~A20M), U3.153 (~GATE_A20); also elsewhere on the board
~KBC_RC: U3.155 (~KBC_RC); also elsewhere on the board
~MEMCS16: U3.36 (~MEMCS16); also elsewhere on the board
~MEMR: U3.192 (~MEMR); also elsewhere on the board
~MEMW: U3.193 (~MEMW); also elsewhere on the board
~MWE: U3.110 (~MWE); also elsewhere on the board
~RAS01: U3.102 (~RAS01); also elsewhere on the board
~RAS23: U3.103 (~RAS23); also elsewhere on the board
~READY: J14.8, R23.2, U1.7 (~READY), U2.49 (~READY), U3.80 (~READY), U7.9
~REFRESH: U3.6 (~REFRESH); also elsewhere on the board
~RESET: U3.157 (~RESET), U7.5; also elsewhere on the board
~RTC_IRQ8: U3.159 (~RTC_IRQ8); also elsewhere on the board
~SBHE: U3.189 (~SBHE); also elsewhere on the board
~SMEMR: U3.194 (~SMEMR); also elsewhere on the board
~SMEMW: U3.195 (~SMEMW); also elsewhere on the board

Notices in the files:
KiCad/AT386SX.kicad_pcb:
Copyright (C) 2024-2026 Sergey Kiselev
